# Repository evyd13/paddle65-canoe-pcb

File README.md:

# Paddle65

***This PCB design has not been tested yet***

## About
The Paddle65 is a no-frills replacement PCB for the Canoe (gen 1) by Percent Studios. It should fit the case without any modifications.

## Manufacturing
You know the drill ;)

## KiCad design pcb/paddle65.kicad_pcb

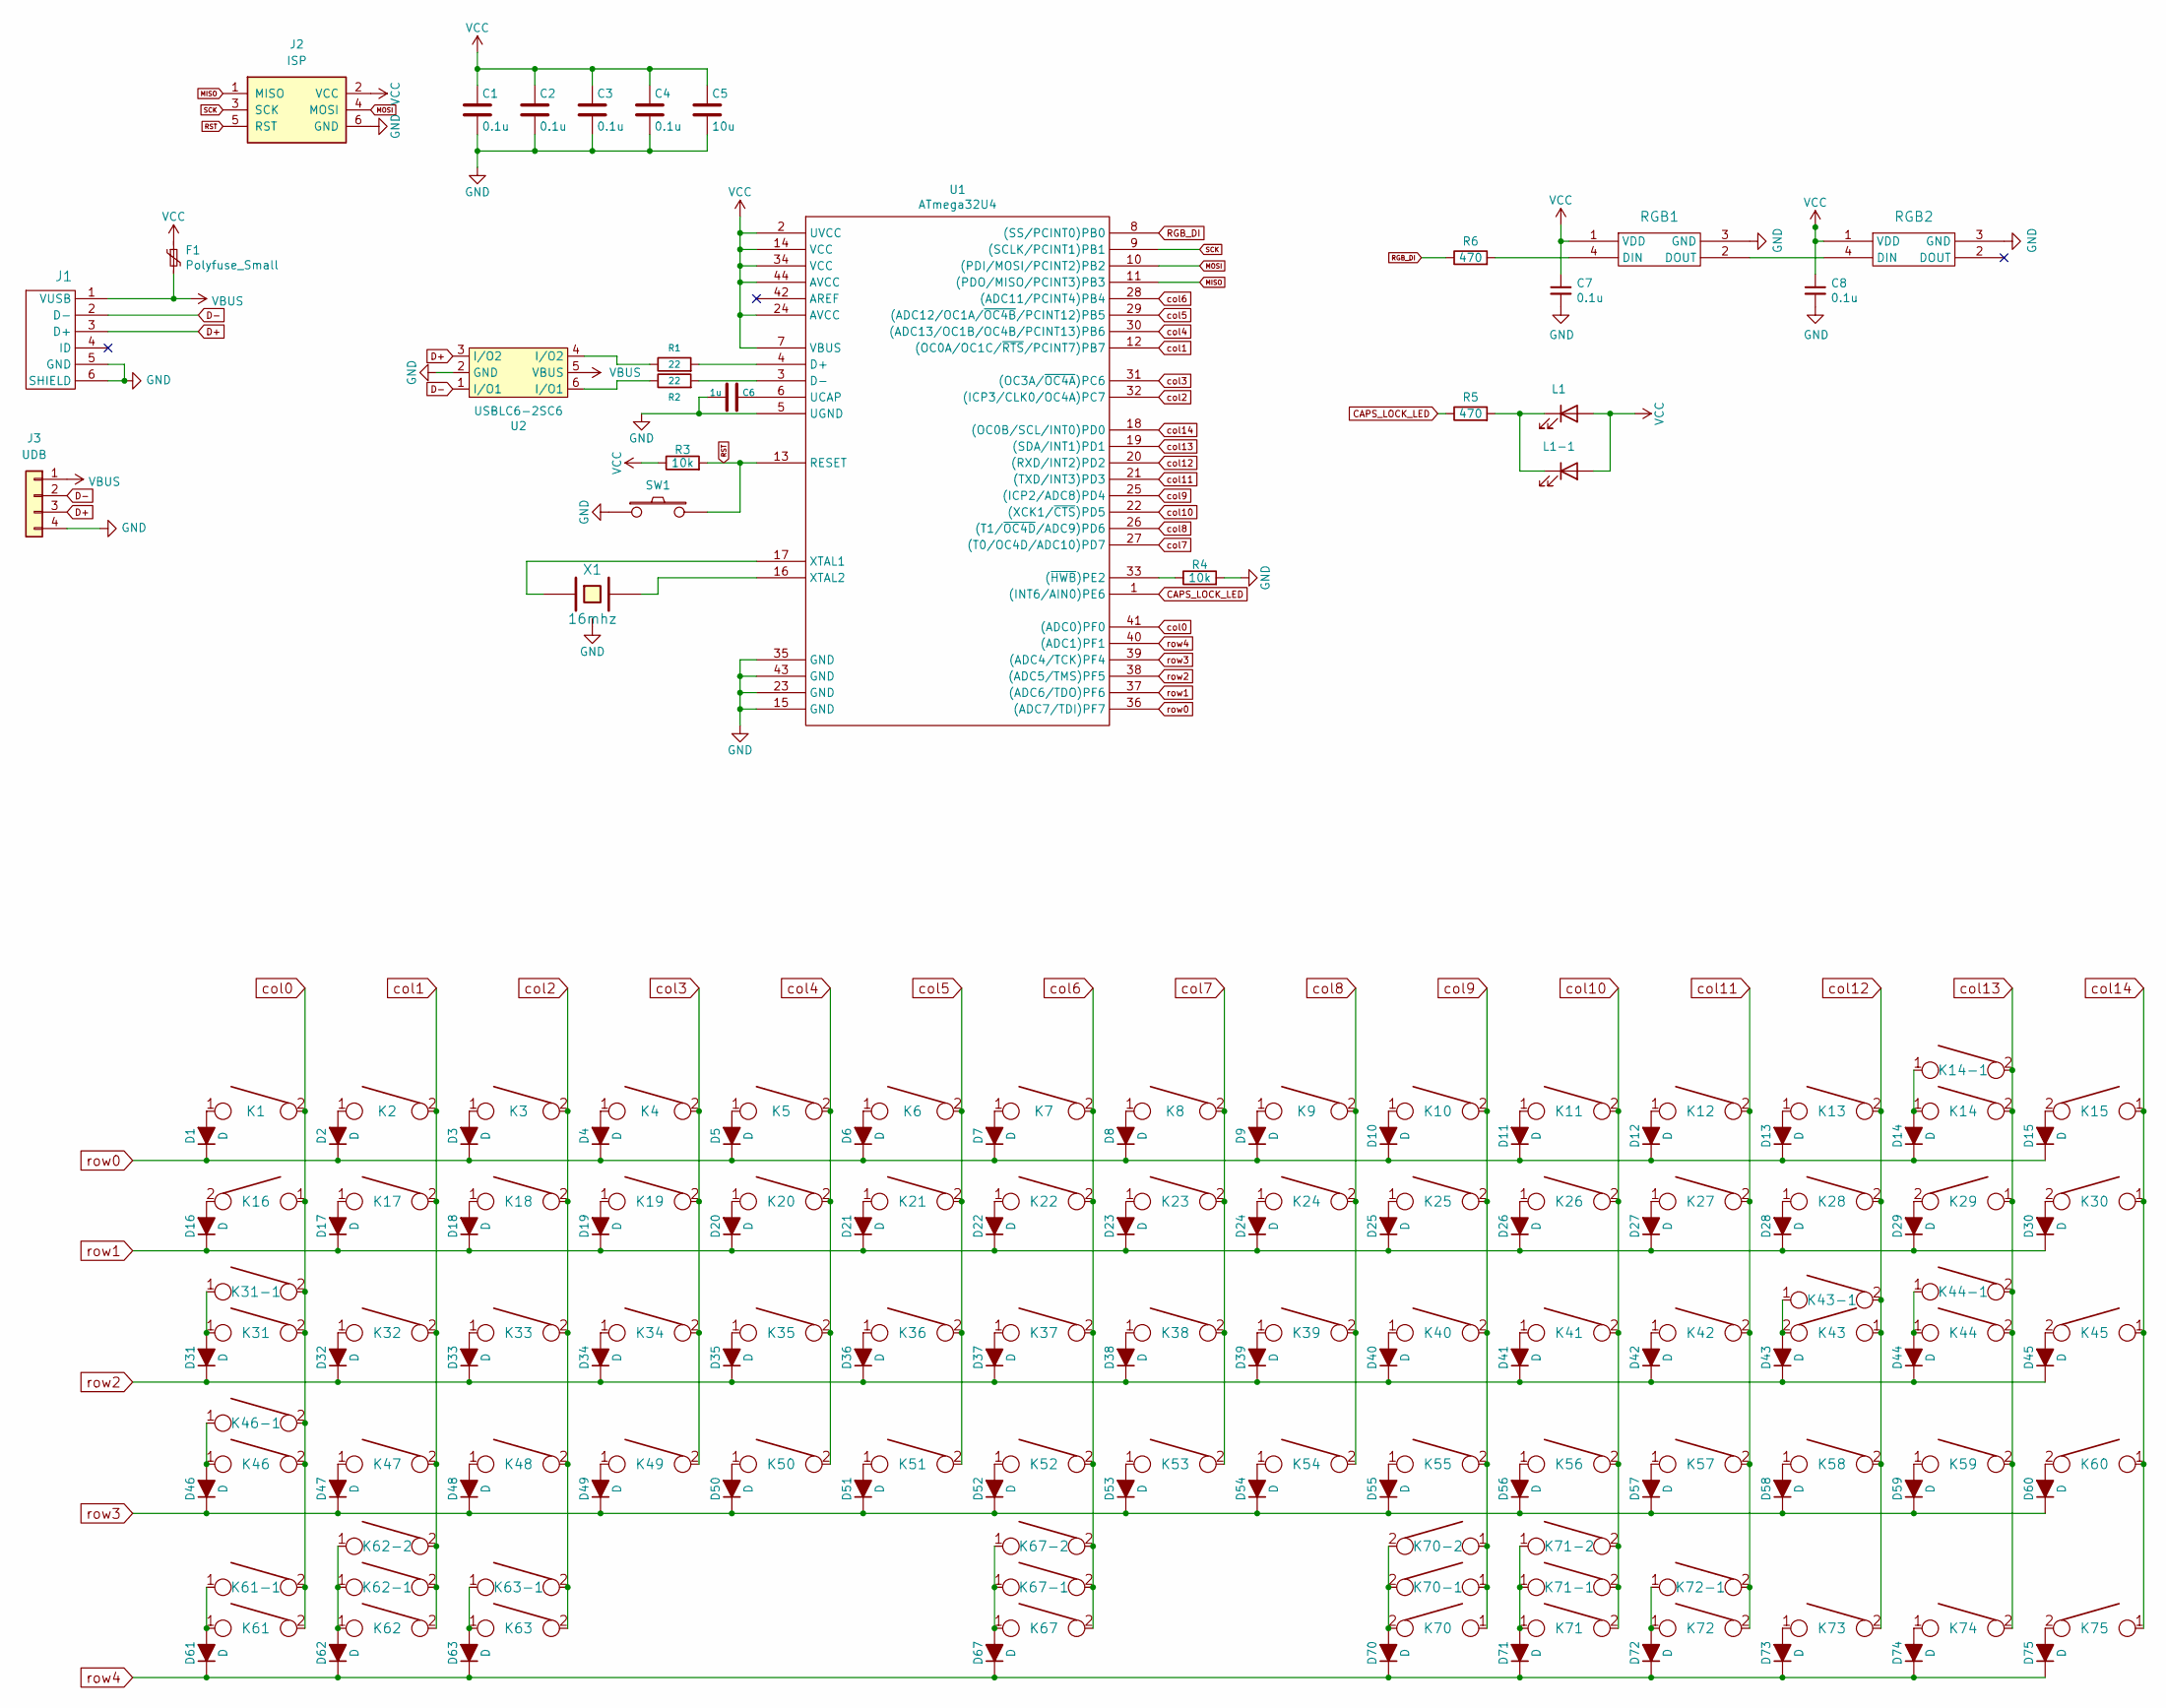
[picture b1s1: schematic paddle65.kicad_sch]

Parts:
C1, C2, C3, C4, C7, C8: 0.1u; C_0805
C5: 10u; C_0805
C6: 1u; C_0805
D1, D2, D3, D4, D5, D6, D7, D8, D9, D10, D11, D12, D13, D14, D15, D16, D17, D18, D19, D20, D21, D22, D23, D24, D25, D26, D27, D28, D29, D30, D31, D32, D33, D34, D35, D36, D37, D38, D39, D40, D41, D42, D43, D44, D45, D46, D47, D48, D49, D50, D51, D52, D53, D54, D55, D56, D57, D58, D59, D60, D61, D62, D63, D67, D70, D71, D72, D73, D74, D75: D; D_0805
F1: Polyfuse_Small; R_0805
J1: USB_mini_micro_B; CONN_UX60SC-MB-5S8
J2: ISP; CONN_isp_standard
J3: UDB; CONN_JST_SH_SM04B-SRSS-TB_1x04-1MP_P1.00mm_Horizontal
K1, K2, K3, K4, K5, K6, K7, K8, K9, K10, K11, K12, K13, K14-1, K15, K17, K18, K19, K20, K21, K22, K23, K24, K25, K26, K27, K28, K29, K30, K32, K33, K34, K35, K36, K37, K38, K39, K40, K41, K42, K43, K45, K47, K48, K49, K50, K51, K52, K53, K54, K55, K56, K57, K59, K60, K62-1, K70-1, K71-2, K72, K73, K74, K75: KEYSW; CHERRY_PLATE_100H
K14: KEYSW; CHERRY_PCB_200H
K16, K43-1, K61-1, K62-2, K63-1, K70-2, K71-1, K72-1: KEYSW; CHERRY_PLATE_150H
K31, K58: KEYSW; CHERRY_PLATE_175H
K31-1, K46-1, K61, K62, K63, K70, K71: KEYSW; CHERRY_PLATE_125H
K44, K46: KEYSW; CHERRY_PCB_225H
K44-1: KEYSW; CHERRY_PCB_200H_V
K67: KEYSW; CHERRY_PCB_625H_F
K67-1, K67-2: KEYSW; CHERRY_PCB_700H_F
L1, L1-1: LED; CHERRY_MX_LED_neo
R1, R2: 22; R_0805
R3, R4: 10k; R_0805
R5, R6: 470; R_0805
RGB1, RGB2: SK6812MINI-E; LED_SK6812MINI-E
SW1: SW_PUSH; SWITCH_SPST_TL3342
U1: ATmega32U4; MCU_ATMEGA32U4-AU
U2: USBLC6-2SC6; PACKAGE_SOT-23-6
X1: 16mhz; XTAL_SMD_Murata_CSTxExxV-3Pin_3.0x1.1mm

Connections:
CAPS_LOCK_LED: R5.1, U1.1 ((INT6/AIN0)PE6)
D+: J1.3 (D+), J3.3, U2.3 (I/O2)
D-: J1.2 (D-), J3.2, U2.1 (I/O1)
GND: C1.2, C2.2, C3.2, C4.2, C5.2, C6.2, C7.2, C8.2, J1.5 (GND), J1.6 (SHIELD), J2.6 (GND), J3.4, R4.2, RGB1.3 (GND), RGB2.3 (GND), SW1.1, U1.5 (UGND), U1.15 (GND), U1.23 (GND), U1.35 (GND), U1.43 (GND), U2.2 (GND), X1.3
MISO: J2.1 (MISO), U1.11 ((PDO/MISO/PCINT3)PB3)
MOSI: J2.4 (MOSI), U1.10 ((PDI/MOSI/PCINT2)PB2)
unnamed: C6.1, U1.6 (UCAP)
unnamed: D1.2 (A), K1.1
unnamed: D2.2 (A), K2.1
unnamed: D3.2 (A), K3.1
unnamed: D4.2 (A), K4.1
unnamed: D5.2 (A), K5.1
unnamed: D6.2 (A), K6.1
unnamed: D7.2 (A), K7.1
unnamed: D8.2 (A), K8.1
unnamed: D9.2 (A), K9.1
unnamed: D10.2 (A), K10.1
unnamed: D11.2 (A), K11.1
unnamed: D12.2 (A), K12.1
unnamed: D13.2 (A), K13.1
unnamed: D14.2 (A), K14.1, K14-1.1
unnamed: D15.2 (A), K15.2
unnamed: D16.2 (A), K16.2
unnamed: D17.2 (A), K17.1
unnamed: D18.2 (A), K18.1
unnamed: D19.2 (A), K19.1
unnamed: D20.2 (A), K20.1
unnamed: D21.2 (A), K21.1
unnamed: D22.2 (A), K22.1
unnamed: D23.2 (A), K23.1
unnamed: D24.2 (A), K24.1
unnamed: D25.2 (A), K25.1
unnamed: D26.2 (A), K26.1
unnamed: D27.2 (A), K27.1
unnamed: D28.2 (A), K28.1
unnamed: D29.2 (A), K29.2
unnamed: D30.2 (A), K30.2
unnamed: D31.2 (A), K31.1, K31-1.1
unnamed: D32.2 (A), K32.1
unnamed: D33.2 (A), K33.1
unnamed: D34.2 (A), K34.1
unnamed: D35.2 (A), K35.1
unnamed: D36.2 (A), K36.1
unnamed: D37.2 (A), K37.1
unnamed: D38.2 (A), K38.1
unnamed: D39.2 (A), K39.1
unnamed: D40.2 (A), K40.1
unnamed: D41.2 (A), K41.1
unnamed: D42.2 (A), K42.1
unnamed: D43.2 (A), K43.2, K43-1.1
unnamed: D44.2 (A), K44.1, K44-1.1
unnamed: D45.2 (A), K45.2
unnamed: D46.2 (A), K46.1, K46-1.1
unnamed: D47.2 (A), K47.1
unnamed: D48.2 (A), K48.1
unnamed: D49.2 (A), K49.1
unnamed: D50.2 (A), K50.1
unnamed: D51.2 (A), K51.1
unnamed: D52.2 (A), K52.1
unnamed: D53.2 (A), K53.1
unnamed: D54.2 (A), K54.1
unnamed: D55.2 (A), K55.1
unnamed: D56.2 (A), K56.1
unnamed: D57.2 (A), K57.1
unnamed: D58.2 (A), K58.1
unnamed: D59.2 (A), K59.1
unnamed: D60.2 (A), K60.2
unnamed: D61.2 (A), K61.1, K61-1.1
unnamed: D62.2 (A), K62.1, K62-1.1, K62-2.1
unnamed: D63.2 (A), K63.1, K63-1.1
unnamed: D67.2 (A), K67.1, K67-1.1, K67-2.1
unnamed: D70.2 (A), K70.2, K70-1.2, K70-2.2
unnamed: D71.2 (A), K71.1, K71-1.1, K71-2.1
unnamed: D72.2 (A), K72.1, K72-1.1
unnamed: D73.2 (A), K73.1
unnamed: D74.2 (A), K74.1
unnamed: D75.2 (A), K75.2
unnamed: L1.1 (K), L1-1.1 (K), R5.2
unnamed: R1.1, U2.4 (I/O2)
unnamed: R1.2, U1.4 (D+)
unnamed: R2.1, U2.6 (I/O1)
unnamed: R2.2, U1.3 (D-)
unnamed: R4.1, U1.33 ((~HWB)PE2)
unnamed: R6.2, RGB1.4 (DIN)
unnamed: RGB1.2 (DOUT), RGB2.4 (DIN)
unnamed: U1.16 (XTAL2), X1.2
unnamed: U1.17 (XTAL1), X1.1
RGB_DI: R6.1, U1.8 ((SS/PCINT0)PB0)
RST: J2.5 (RST), R3.2, SW1.2, U1.13 (RESET)
SCK: J2.3 (SCK), U1.9 ((SCLK/PCINT1)PB1)
VBUS: F1.2, J1.1 (VUSB), J3.1, U2.5 (VBUS)
VCC: C1.1, C2.1, C3.1, C4.1, C5.1, C7.1, C8.1, F1.1, J2.2 (VCC), L1.2 (A), L1-1.2 (A), R3.1, RGB1.1 (VDD), RGB2.1 (VDD), U1.2 (UVCC), U1.7 (VBUS), U1.14 (VCC), U1.24 (AVCC), U1.34 (VCC), U1.44 (AVCC)
col0: K1.2, K16.1, K31.2, K31-1.2, K46.2, K46-1.2, K61.2, K61-1.2, U1.41 ((ADC0)PF0)
col1: K2.2, K17.2, K32.2, K47.2, K62.2, K62-1.2, K62-2.2, U1.12 ((OC0A/OC1C/~RTS/PCINT7)PB7)
col2: K3.2, K18.2, K33.2, K48.2, K63.2, K63-1.2, U1.32 ((ICP3/CLK0/OC4A)PC7)
col3: K4.2, K19.2, K34.2, K49.2, U1.31 ((OC3A/~OC4A)PC6)
col4: K5.2, K20.2, K35.2, K50.2, U1.30 ((ADC13/OC1B/OC4B/PCINT13)PB6)
col5: K6.2, K21.2, K36.2, K51.2, U1.29 ((ADC12/OC1A/~OC4B/PCINT12)PB5)
col6: K7.2, K22.2, K37.2, K52.2, K67.2, K67-1.2, K67-2.2, U1.28 ((ADC11/PCINT4)PB4)
col7: K8.2, K23.2, K38.2, K53.2, U1.27 ((T0/OC4D/ADC10)PD7)
col8: K9.2, K24.2, K39.2, K54.2, U1.26 ((T1/~OC4D/ADC9)PD6)
col9: K10.2, K25.2, K40.2, K55.2, K70.1, K70-1.1, K70-2.1, U1.25 ((ICP2/ADC8)PD4)
col10: K11.2, K26.2, K41.2, K56.2, K71.2, K71-1.2, K71-2.2, U1.22 ((XCK1/~CTS)PD5)
col11: K12.2, K27.2, K42.2, K57.2, K72.2, K72-1.2, U1.21 ((TXD/INT3)PD3)
col12: K13.2, K28.2, K43.1, K43-1.2, K58.2, K73.2, U1.20 ((RXD/INT2)PD2)
col13: K14.2, K14-1.2, K29.1, K44.2, K44-1.2, K59.2, K74.2, U1.19 ((SDA/INT1)PD1)
col14: K15.1, K30.1, K45.1, K60.1, K75.1, U1.18 ((OC0B/SCL/INT0)PD0)
row0: D1.1 (K), D2.1 (K), D3.1 (K), D4.1 (K), D5.1 (K), D6.1 (K), D7.1 (K), D8.1 (K), D9.1 (K), D10.1 (K), D11.1 (K), D12.1 (K), D13.1 (K), D14.1 (K), D15.1 (K), U1.36 ((ADC7/TDI)PF7)
row1: D16.1 (K), D17.1 (K), D18.1 (K), D19.1 (K), D20.1 (K), D21.1 (K), D22.1 (K), D23.1 (K), D24.1 (K), D25.1 (K), D26.1 (K), D27.1 (K), D28.1 (K), D29.1 (K), D30.1 (K), U1.37 ((ADC6/TDO)PF6)
row2: D31.1 (K), D32.1 (K), D33.1 (K), D34.1 (K), D35.1 (K), D36.1 (K), D37.1 (K), D38.1 (K), D39.1 (K), D40.1 (K), D41.1 (K), D42.1 (K), D43.1 (K), D44.1 (K), D45.1 (K), U1.38 ((ADC5/TMS)PF5)
row3: D46.1 (K), D47.1 (K), D48.1 (K), D49.1 (K), D50.1 (K), D51.1 (K), D52.1 (K), D53.1 (K), D54.1 (K), D55.1 (K), D56.1 (K), D57.1 (K), D58.1 (K), D59.1 (K), D60.1 (K), U1.39 ((ADC4/TCK)PF4)
row4: D61.1 (K), D62.1 (K), D63.1 (K), D67.1 (K), D70.1 (K), D71.1 (K), D72.1 (K), D73.1 (K), D74.1 (K), D75.1 (K), U1.40 ((ADC1)PF1)

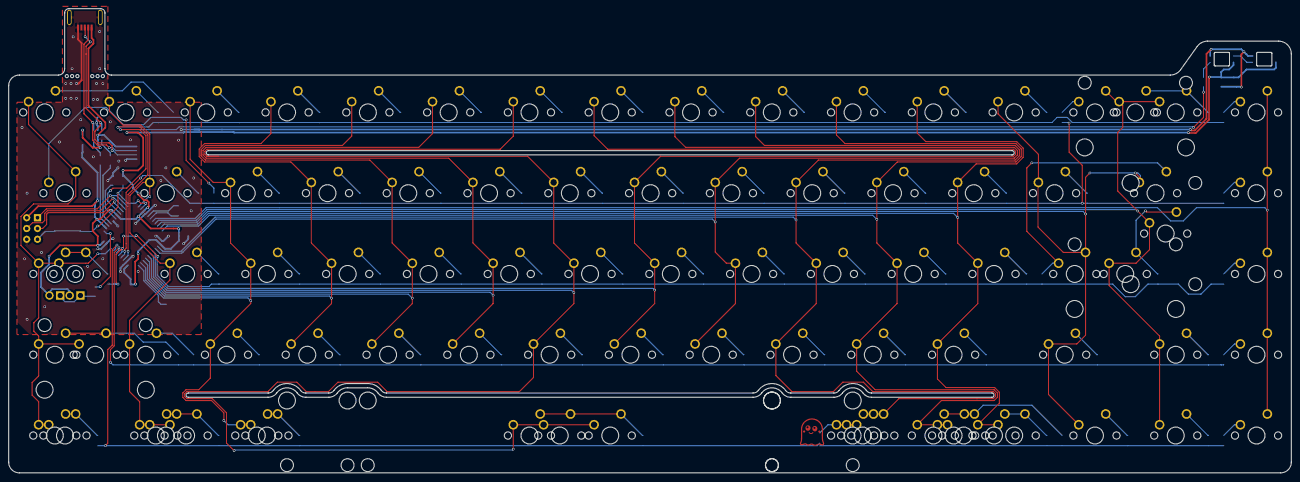
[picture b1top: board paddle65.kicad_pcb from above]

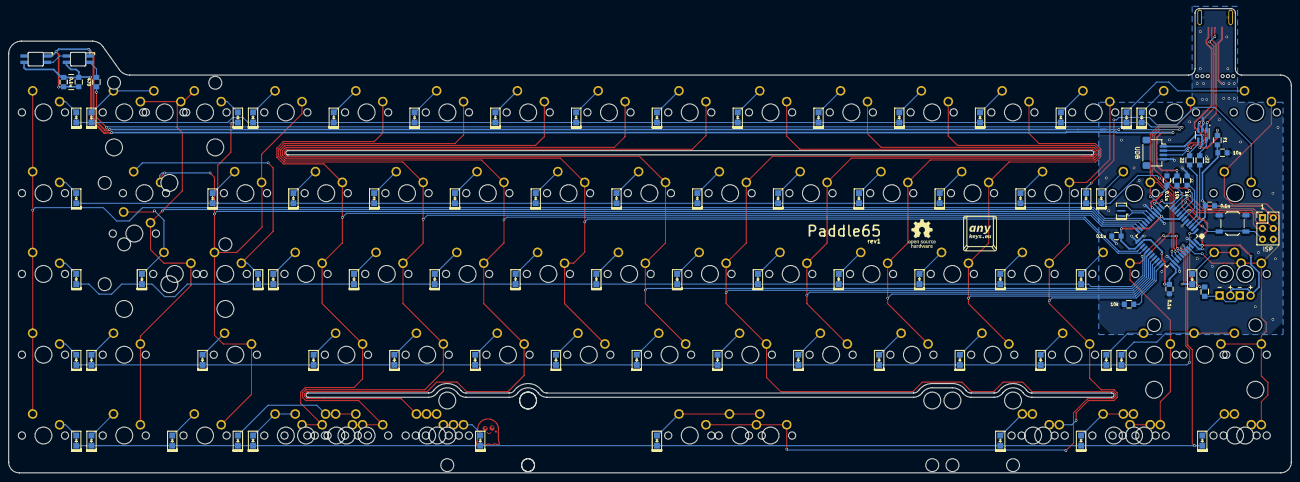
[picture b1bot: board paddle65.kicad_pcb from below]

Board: 2 copper layers, 302.5 x 109.5 mm, 182 parts (93 on the bottom side), 112 nets.

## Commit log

2022-03-06 Upload PCB files
2022-03-06 Add plate & small pcb fixes
